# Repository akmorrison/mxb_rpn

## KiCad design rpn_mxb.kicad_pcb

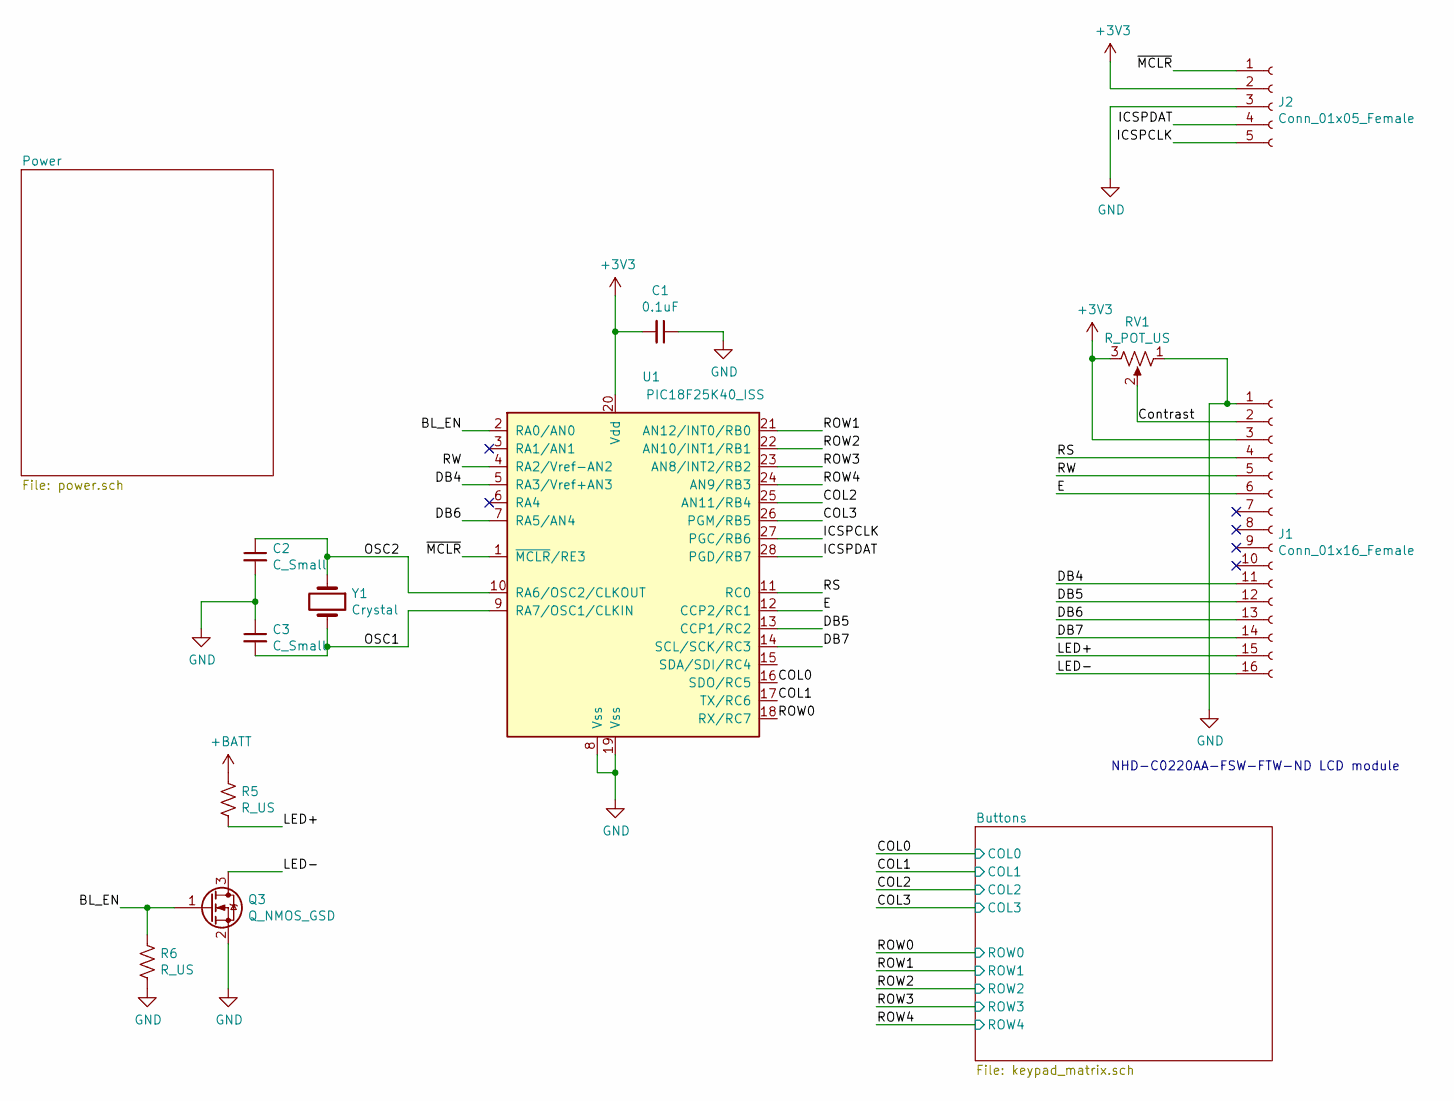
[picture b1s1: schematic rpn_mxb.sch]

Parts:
C1: 0.1uF; C_0805_2012Metric_Pad1.15x1.40mm_HandSolder
C2, C3: C_Small; C_0805_2012Metric_Pad1.15x1.40mm_HandSolder
J1: Conn_01x16_Female; PinHeader_2x08_P1.27mm_Horizontal
J2: Conn_01x05_Female; PinSocket_1x05_P2.54mm_Horizontal
Q3: Q_NMOS_GSD; SOT-23_Handsoldering
R5, R6: R_US; R_0805_2012Metric_Pad1.15x1.40mm_HandSolder
RV1: R_POT_US; Potentiometer_ACP_CA9-V10_Vertical
U1: PIC18F25K40_ISS; SOIC-28W_7.5x18.7mm_P1.27mm
Y1: Crystal; Crystal_HC49-4H_Vertical

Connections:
+3V3: C1.2, J1.3, J2.2, RV1.3, U1.20 (Vdd); also elsewhere on the board
+BATT: R5.1; also elsewhere on the board
/BL_EN: Q3.1 (G), R6.1, U1.2 (RA0/AN0)
/COL0: U1.16 (SDO/RC5); also elsewhere on the board
/COL1: U1.17 (TX/RC6); also elsewhere on the board
/COL2: U1.25 (AN11/RB4); also elsewhere on the board
/COL3: U1.26 (PGM/RB5); also elsewhere on the board
/Contrast: J1.2, RV1.2
/DB4: J1.11, U1.5 (RA3/Vref+AN3)
/DB5: J1.12, U1.13 (CCP1/RC2)
/DB6: J1.13, U1.7 (RA5/AN4)
/DB7: J1.14, U1.14 (SCL/SCK/RC3)
/E: J1.6, U1.12 (CCP2/RC1)
/ICSPCLK: J2.5, U1.27 (PGC/RB6)
/ICSPDAT: J2.4, U1.28 (PGD/RB7)
/LED+: J1.15, R5.2
/LED-: J1.16, Q3.3 (D)
/OSC1: C3.2, U1.9 (RA7/OSC1/CLKIN), Y1.2
/OSC2: C2.1, U1.10 (RA6/OSC2/CLKOUT), Y1.1
/ROW0: U1.18 (RX/RC7); also elsewhere on the board
/ROW1: U1.21 (AN12/INT0/RB0); also elsewhere on the board
/ROW2: U1.22 (AN10/INT1/RB1); also elsewhere on the board
/ROW3: U1.23 (AN8/INT2/RB2); also elsewhere on the board
/ROW4: U1.24 (AN9/RB3); also elsewhere on the board
/RS: J1.4, U1.11 (RC0)
/RW: J1.5, U1.4 (RA2/Vref-AN2)
/~MCLR: J2.1, U1.1 (~MCLR~/RE3)
GND: C1.1, C2.2, C3.1, J1.1, J2.3, Q3.2 (S), R6.2, RV1.1, U1.8 (Vss), U1.19 (Vss); also elsewhere on the board

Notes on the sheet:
NHD-C0220AA-FSW-FTW-ND LCD module

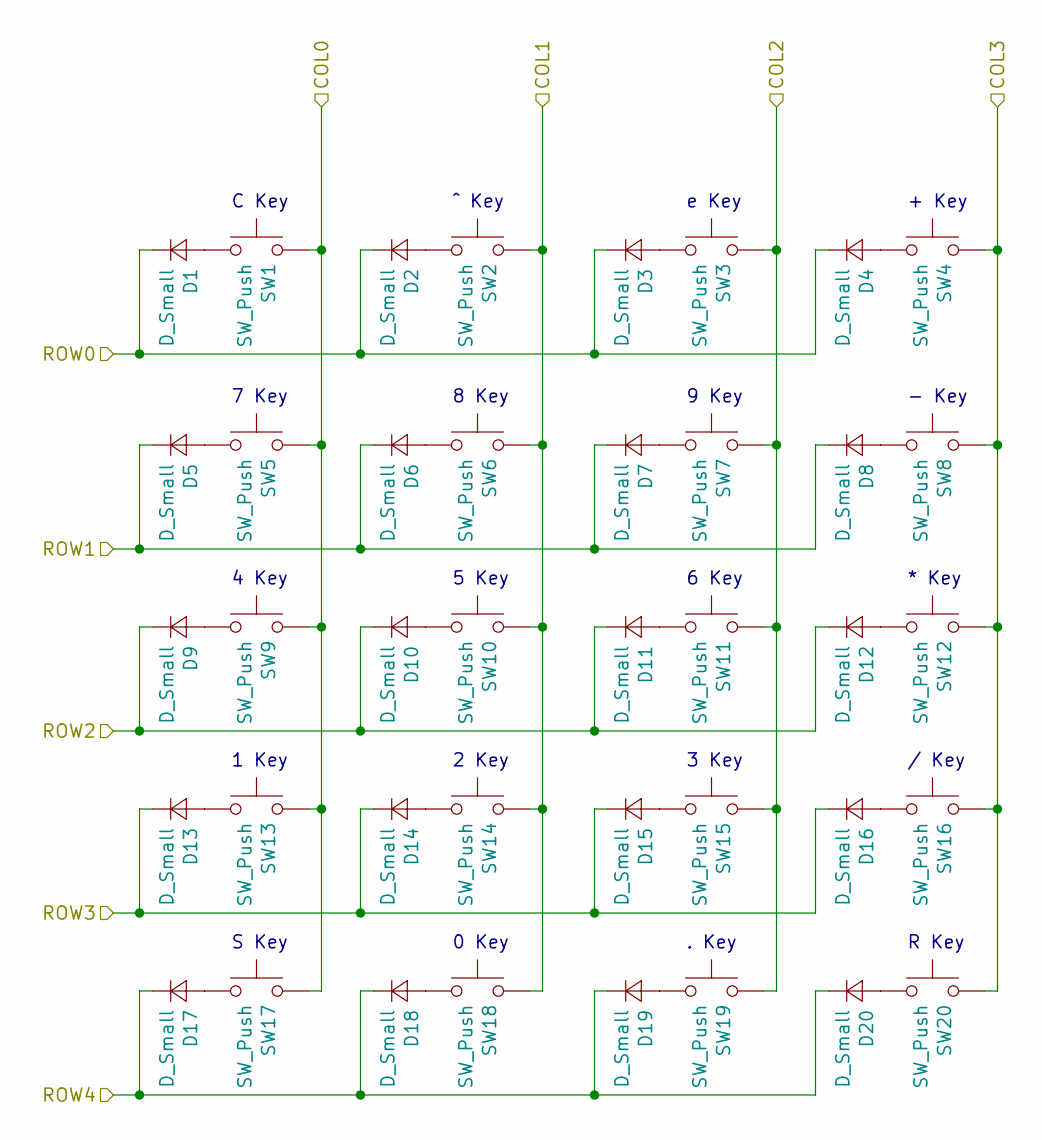
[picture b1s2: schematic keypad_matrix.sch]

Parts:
D1, D2, D3, D4, D5, D6, D7, D8, D9, D10, D11, D12, D13, D14, D15, D16, D17, D18, D19, D20: D_Small; D_0603_1608Metric_Pad1.05x0.95mm_HandSolder
SW1, SW2, SW3, SW4, SW5, SW6, SW7, SW8, SW9, SW10, SW11, SW12, SW13, SW14, SW15, SW16, SW17, SW18, SW19, SW20: SW_Push; SW_Cherry_MX1A_1.00u_PCB

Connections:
/COL0: SW1.2, SW5.2, SW9.2, SW13.2, SW17.2; also elsewhere on the board
/COL1: SW2.2, SW6.2, SW10.2, SW14.2, SW18.2; also elsewhere on the board
/COL2: SW3.2, SW7.2, SW11.2, SW15.2, SW19.2; also elsewhere on the board
/COL3: SW4.2, SW8.2, SW12.2, SW16.2, SW20.2; also elsewhere on the board
/ROW0: D1.1 (K), D2.1 (K), D3.1 (K), D4.1 (K); also elsewhere on the board
/ROW1: D5.1 (K), D6.1 (K), D7.1 (K), D8.1 (K); also elsewhere on the board
/ROW2: D9.1 (K), D10.1 (K), D11.1 (K), D12.1 (K); also elsewhere on the board
/ROW3: D13.1 (K), D14.1 (K), D15.1 (K), D16.1 (K); also elsewhere on the board
/ROW4: D17.1 (K), D18.1 (K), D19.1 (K), D20.1 (K); also elsewhere on the board
unnamed: D1.2 (A), SW1.1
unnamed: D2.2 (A), SW2.1
unnamed: D3.2 (A), SW3.1
unnamed: D4.2 (A), SW4.1
unnamed: D5.2 (A), SW5.1
unnamed: D6.2 (A), SW6.1
unnamed: D7.2 (A), SW7.1
unnamed: D8.2 (A), SW8.1
unnamed: D9.2 (A), SW9.1
unnamed: D10.2 (A), SW10.1
unnamed: D11.2 (A), SW11.1
unnamed: D12.2 (A), SW12.1
unnamed: D13.2 (A), SW13.1
unnamed: D14.2 (A), SW14.1
unnamed: D15.2 (A), SW15.1
unnamed: D16.2 (A), SW16.1
unnamed: D17.2 (A), SW17.1
unnamed: D18.2 (A), SW18.1
unnamed: D19.2 (A), SW19.1
unnamed: D20.2 (A), SW20.1

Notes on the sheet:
R Key
. Key
0 Key
S Key
/ Key
3 Key
2 Key
1 Key
* Key
6 Key
5 Key
4 Key
+ Key
e Key
^ Key
C Key
- Key
9 Key
8 Key
7 Key

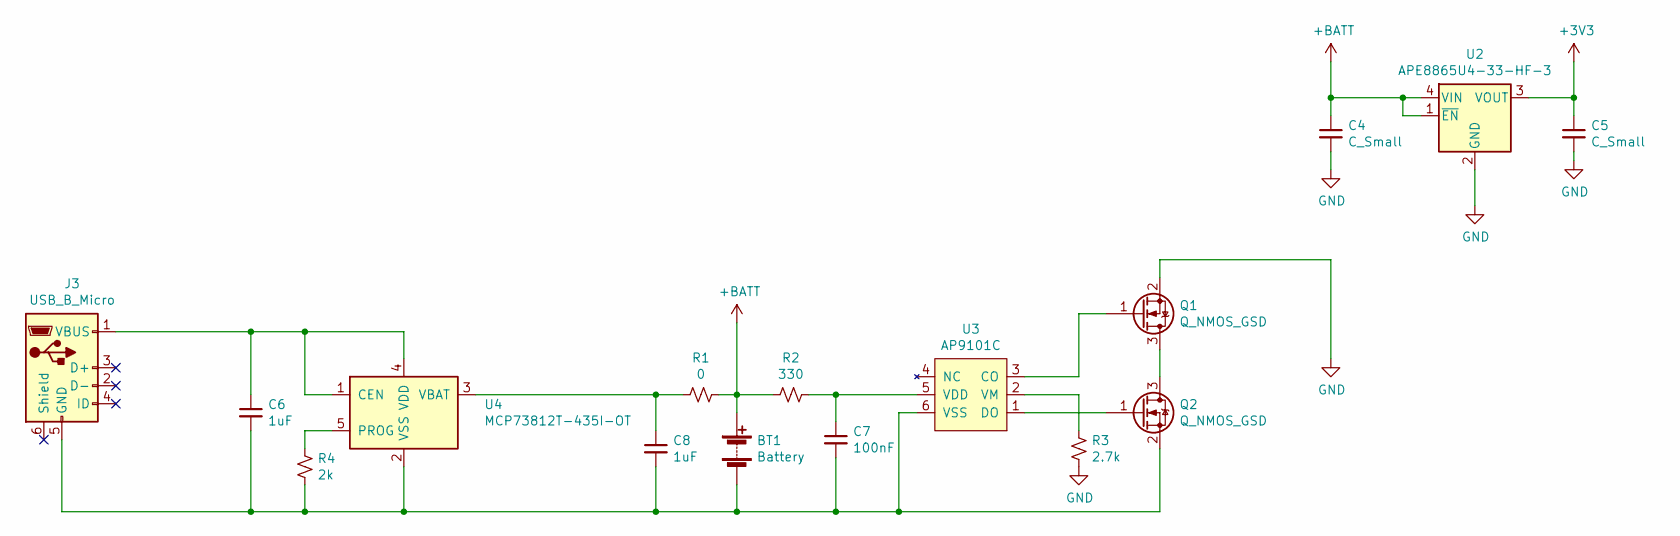
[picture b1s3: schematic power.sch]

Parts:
BT1: Battery; JST_EH_B02B-EH-A_1x02_P2.50mm_Vertical
C4, C5: C_Small; C_0805_2012Metric_Pad1.15x1.40mm_HandSolder
C6, C8: 1uF; C_0805_2012Metric_Pad1.15x1.40mm_HandSolder
C7: 100nF; C_0805_2012Metric_Pad1.15x1.40mm_HandSolder
J3: USB_B_Micro; USB_Micro-B_Amphenol_10103594-0001LF_Horizontal
Q1, Q2: Q_NMOS_GSD; SOT-23_Handsoldering
R1: 0; R_0805_2012Metric_Pad1.15x1.40mm_HandSolder
R2: 330; R_0805_2012Metric_Pad1.15x1.40mm_HandSolder
R3: 2.7k; R_0805_2012Metric_Pad1.15x1.40mm_HandSolder
R4: 2k; R_0805_2012Metric_Pad1.15x1.40mm_HandSolder
U2: APE8865U4-33-HF-3; SOT-23-5_HandSoldering
U3: AP9101C; SOT-23-6_Handsoldering
U4: MCP73812T-435I-OT; SOT-23-5_HandSoldering

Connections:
+3V3: C5.1, U2.3 (VOUT); also elsewhere on the board
+BATT: BT1.1 (+), C4.1, R1.1, R2.2, U2.1 (~EN~), U2.4 (VIN); also elsewhere on the board
GND: C4.2, C5.2, Q1.2 (S), R3.1, U2.2 (GND); also elsewhere on the board
unnamed: BT1.2 (-), C6.2, C7.2, C8.2, J3.5 (GND), Q2.2 (S), R4.2, U3.6 (VSS), U4.2 (VSS)
unnamed: C6.1, J3.1 (VBUS), U4.1 (CEN), U4.4 (VDD)
unnamed: C7.1, R2.1, U3.5 (VDD)
unnamed: C8.1, R1.2, U4.3 (VBAT)
unnamed: Q1.1 (G), U3.3 (CO)
unnamed: Q1.3 (D), Q2.3 (D)
unnamed: Q2.1 (G), U3.1 (DO)
unnamed: R3.2, U3.2 (VM)
unnamed: R4.1, U4.5 (PROG)

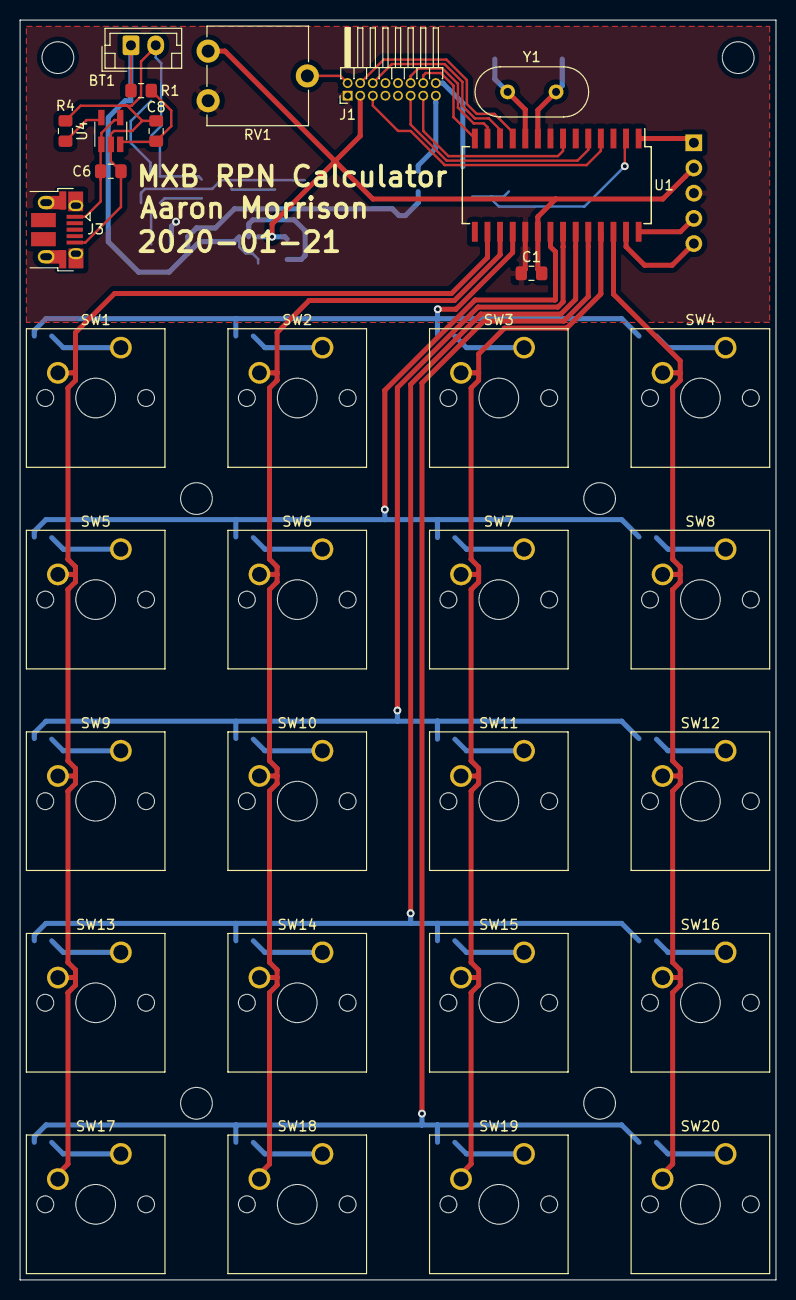
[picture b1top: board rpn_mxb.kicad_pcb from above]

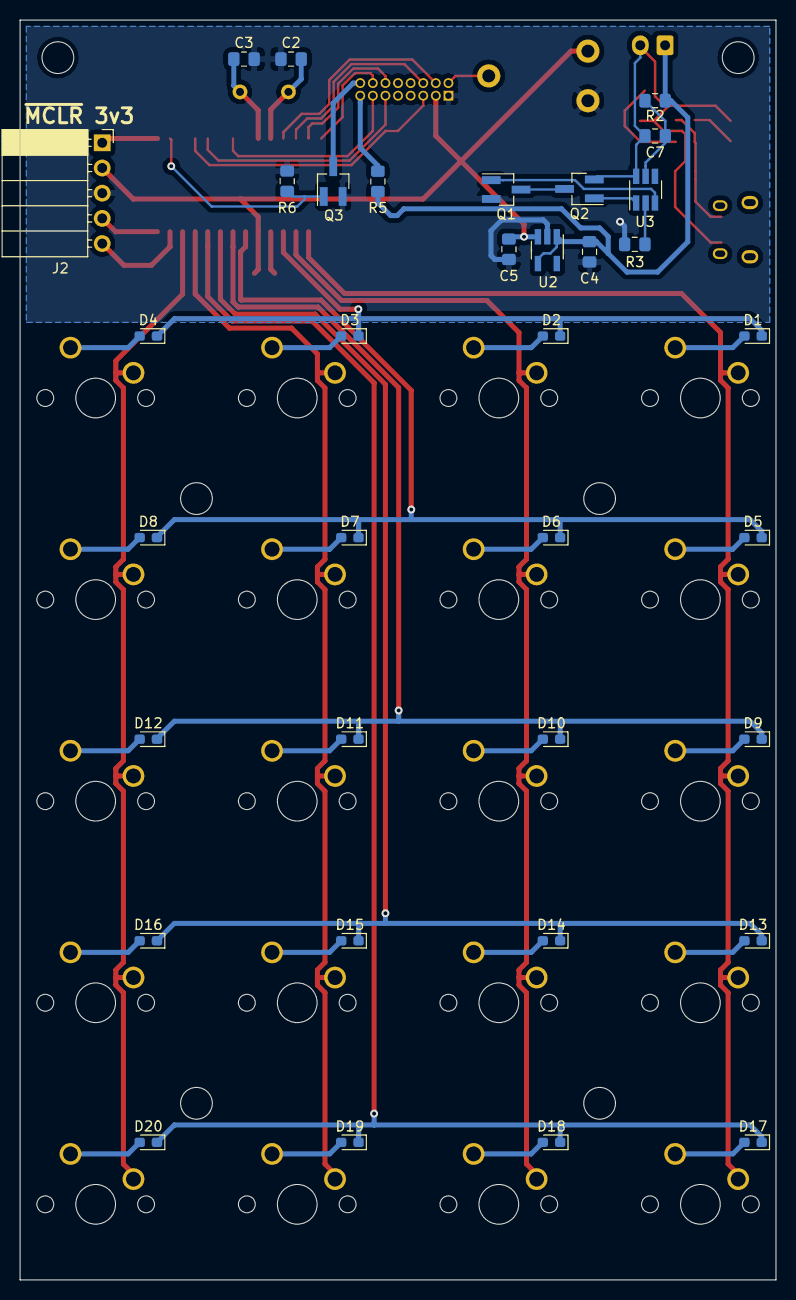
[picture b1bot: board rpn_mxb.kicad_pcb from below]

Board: 2 copper layers, 76.2 x 127.0 mm, 67 parts (35 on the bottom side), 57 nets.

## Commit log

2019-07-04 Initial commit
    I have this idea kicking around in my head for a cherry MX blue
    keyswitch based desk calculator. This is that. The hardware is dead
    fucking simple, the firmware is gonna be fun, the mechanical design is
    gonna be a bitch and a half (need to find a partner to go in on).
    There are problems in this, not everything's connected, one of the
    SOT-23-6's needs to be handsoldering pads, the connector for the LCD is
2020-01-21 DFM version
    Add ability for microcontroller to enable/disable backlight, fix bug
    with where BATT net comes from, create gerbers to submit to DFM.
2020-01-22 Start working on software
2020-02-26 Add TODO comments to schematic based on assemby epiphanies
